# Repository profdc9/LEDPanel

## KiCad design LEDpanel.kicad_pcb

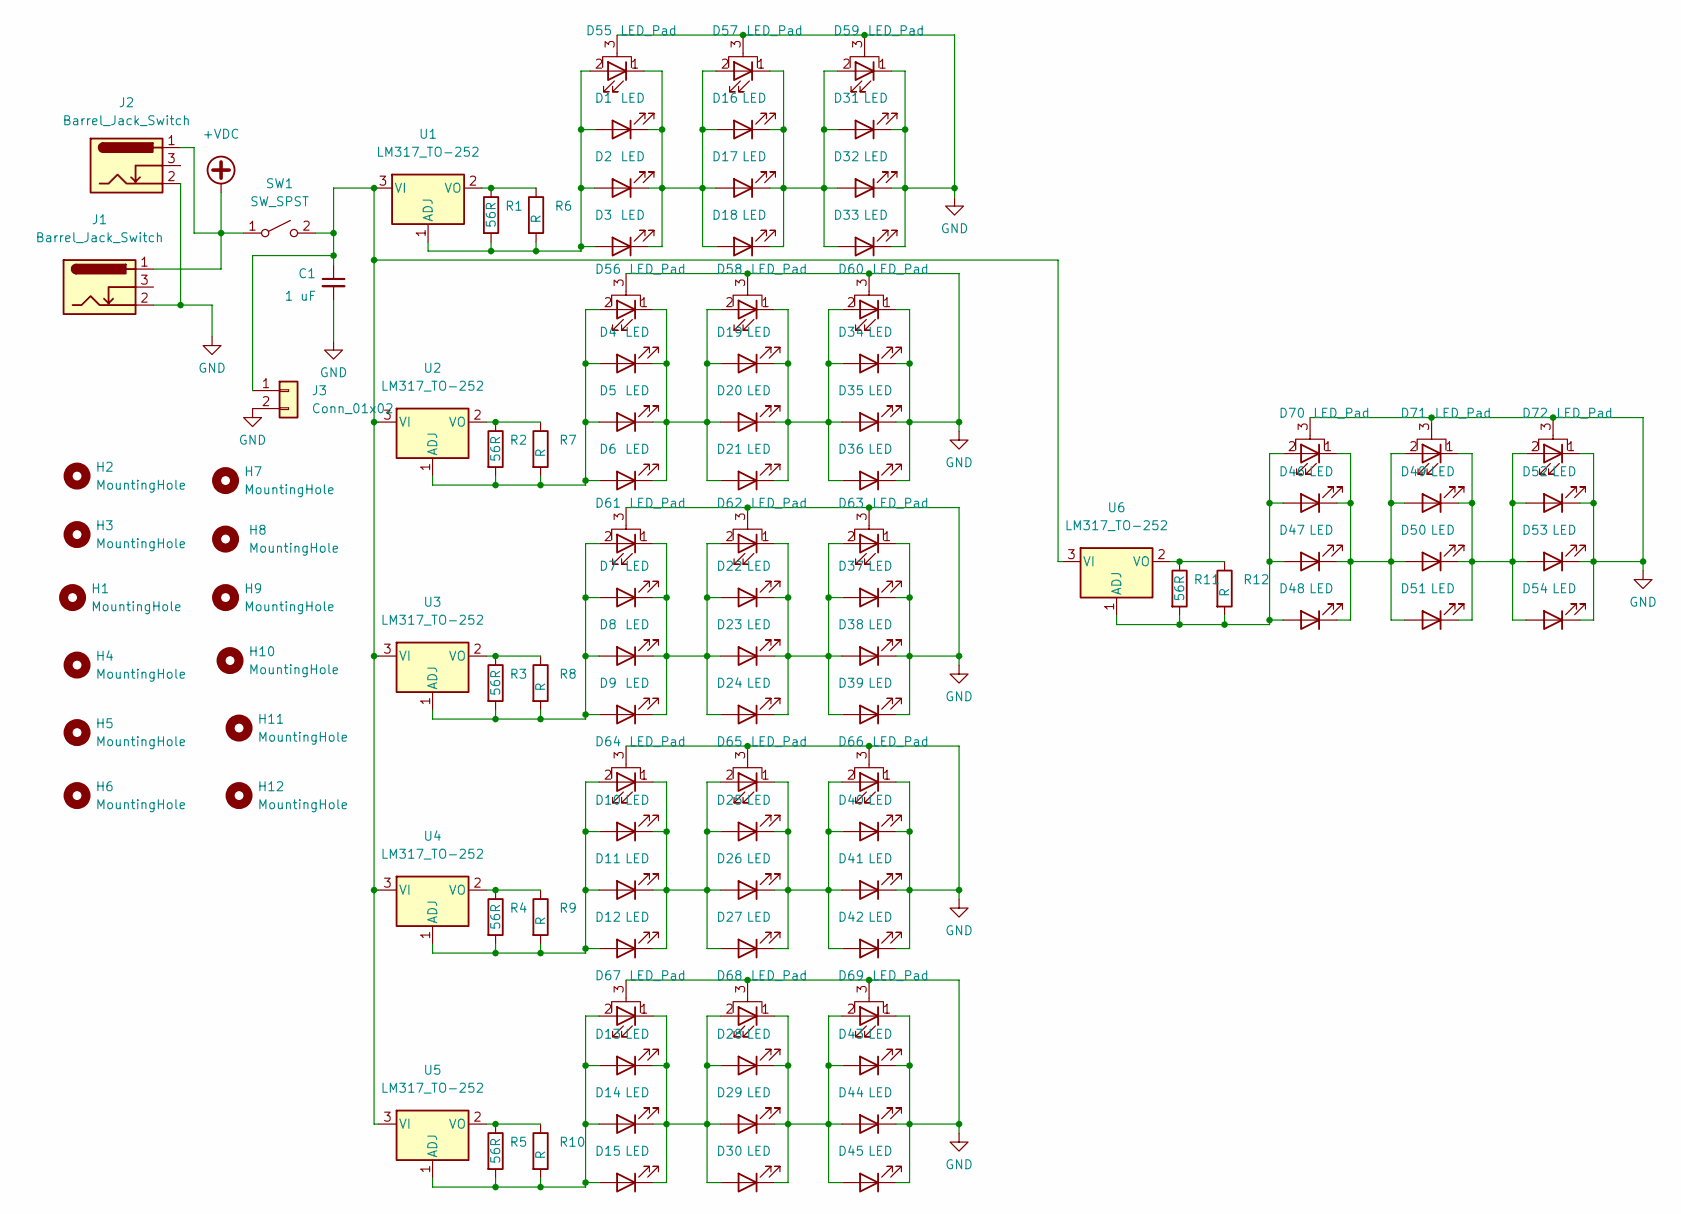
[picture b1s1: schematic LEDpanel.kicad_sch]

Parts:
C1: 1 uF; C_0805_2012Metric_Pad1.18x1.45mm_HandSolder; LCSC C28323
D1, D4, D7, D10, D13, D16, D19, D22, D25, D28, D31, D34, D37, D40, D43, D46, D49, D52: LED; LED_PLCC_2835_Handsoldering
D2, D5, D8, D11, D14, D17, D20, D23, D26, D29, D32, D35, D38, D41, D44, D47, D50, D53: LED; LED_0805_2012Metric_Pad1.15x1.40mm_HandSolder
D3, D6, D9, D12, D15, D18, D21, D24, D27, D30, D33, D36, D39, D42, D45, D48, D51, D54: LED; LED_D3.0mm
D55, D56, D57, D58, D59, D60, D61, D62, D63, D64, D65, D66, D67, D68, D69, D70, D71, D72: LED_Pad; LED_Cree-XP
H1, H4, H5, H6, H7, H9, H11, H12: MountingHole; MountingHole_4mm
H2, H3, H8, H10: MountingHole; MountingHole_3.2mm_M3
J1, J2: Barrel_Jack_Switch; BarrelJack_Horizontal
J3: Conn_01x02; TerminalBlock_Phoenix_MKDS-1,5-2-5.08_1x02_P5.08mm_Horizont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
R1, R2, R3, R4, R5, R11: 56R; R_0805_2012Metric_Pad1.20x1.40mm_HandSolder; LCSC C17757
R6, R7, R8, R9, R10, R12: R; R_Axial_DIN0207_L6.3mm_D2.5mm_P7.62mm_Horizontal
SW1: SW_SPST; TerminalBlock_Phoenix_MKDS-1,5-2-5.08_1x02_P5.08mm_Horizont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
U1, U2, U3, U4, U5, U6: LM317_TO-252; TO-252-2; LCSC C75510

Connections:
+VDC: J1.1, J2.1, SW1.1 (A)
GND: C1.2, D31.1 (K), D32.1 (K), D33.1 (K), D34.1 (K), D35.1 (K), D36.1 (K), D37.1 (K), D38.1 (K), D39.1 (K), D40.1 (K), D41.1 (K), D42.1 (K), D43.1 (K), D44.1 (K), D45.1 (K), D52.1 (K), D53.1 (K), D54.1 (K), D55.3 (PAD), D56.3 (PAD), D57.3 (PAD), D58.3 (PAD), D59.1 (K), D59.3 (PAD), D60.1 (K), D60.3 (PAD), D61.3 (PAD), D62.3 (PAD), D63.1 (K), D63.3 (PAD), D64.3 (PAD), D65.3 (PAD), D66.1 (K), D66.3 (PAD), D67.3 (PAD), D68.3 (PAD), D69.1 (K), D69.3 (PAD), D70.3 (PAD), D71.3 (PAD), D72.1 (K), D72.3 (PAD), J1.2, J2.2, J3.2
unnamed: C1.1, J3.1, SW1.2 (B), U1.3 (VI), U2.3 (VI), U3.3 (VI), U4.3 (VI), U5.3 (VI), U6.3 (VI)
unnamed: D1.1 (K), D2.1 (K), D3.1 (K), D16.2 (A), D17.2 (A), D18.2 (A), D55.1 (K), D57.2 (A)
unnamed: D4.2 (A), D5.2 (A), D6.2 (A), D56.2 (A), R2.2, R7.2, U2.1 (ADJ)
unnamed: D10.1 (K), D11.1 (K), D12.1 (K), D25.2 (A), D26.2 (A), D27.2 (A), D64.1 (K), D65.2 (A)
unnamed: D13.1 (K), D14.1 (K), D15.1 (K), D28.2 (A), D29.2 (A), D30.2 (A), D67.1 (K), D68.2 (A)
unnamed: D13.2 (A), D14.2 (A), D15.2 (A), D67.2 (A), R5.2, R10.2, U5.1 (ADJ)
unnamed: D16.1 (K), D17.1 (K), D18.1 (K), D31.2 (A), D32.2 (A), D33.2 (A), D57.1 (K), D59.2 (A)
unnamed: D19.1 (K), D20.1 (K), D21.1 (K), D34.2 (A), D35.2 (A), D36.2 (A), D58.1 (K), D60.2 (A)
unnamed: D4.1 (K), D5.1 (K), D6.1 (K), D19.2 (A), D20.2 (A), D21.2 (A), D56.1 (K), D58.2 (A)
unnamed: D22.1 (K), D23.1 (K), D24.1 (K), D37.2 (A), D38.2 (A), D39.2 (A), D62.1 (K), D63.2 (A)
unnamed: D7.1 (K), D8.1 (K), D9.1 (K), D22.2 (A), D23.2 (A), D24.2 (A), D61.1 (K), D62.2 (A)
unnamed: D25.1 (K), D26.1 (K), D27.1 (K), D40.2 (A), D41.2 (A), D42.2 (A), D65.1 (K), D66.2 (A)
unnamed: D28.1 (K), D29.1 (K), D30.1 (K), D43.2 (A), D44.2 (A), D45.2 (A), D68.1 (K), D69.2 (A)
unnamed: D46.1 (K), D47.1 (K), D48.1 (K), D49.2 (A), D50.2 (A), D51.2 (A), D70.1 (K), D71.2 (A)
unnamed: D46.2 (A), D47.2 (A), D48.2 (A), D70.2 (A), R11.2, R12.2, U6.1 (ADJ)
unnamed: D49.1 (K), D50.1 (K), D51.1 (K), D52.2 (A), D53.2 (A), D54.2 (A), D71.1 (K), D72.2 (A)
unnamed: R1.1, R6.1, U1.2 (VO)
unnamed: D1.2 (A), D2.2 (A), D3.2 (A), D55.2 (A), R1.2, R6.2, U1.1 (ADJ)
unnamed: R2.1, R7.1, U2.2 (VO)
unnamed: R3.1, R8.1, U3.2 (VO)
unnamed: D7.2 (A), D8.2 (A), D9.2 (A), D61.2 (A), R3.2, R8.2, U3.1 (ADJ)
unnamed: R4.1, R9.1, U4.2 (VO)
unnamed: D10.2 (A), D11.2 (A), D12.2 (A), D64.2 (A), R4.2, R9.2, U4.1 (ADJ)
unnamed: R5.1, R10.1, U5.2 (VO)
unnamed: R11.1, R12.1, U6.2 (VO)

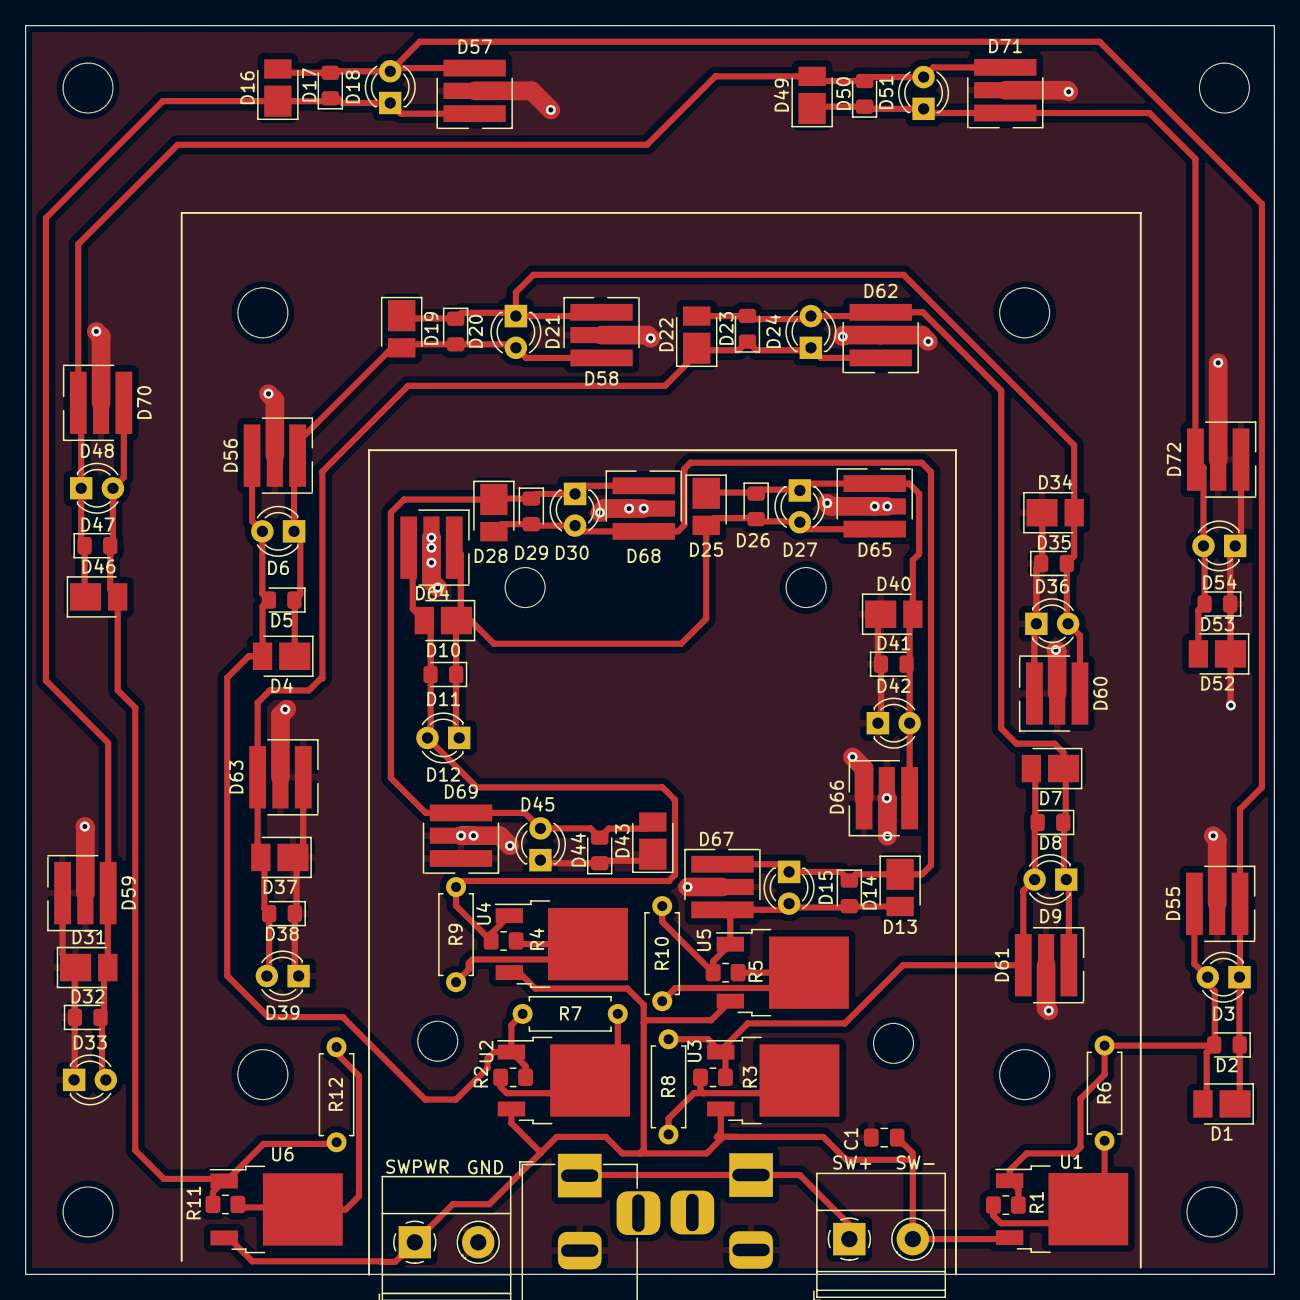
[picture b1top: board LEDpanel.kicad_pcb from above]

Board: 2 copper layers, 100.0 x 100.0 mm, 107 parts (1 on the bottom side), 27 nets.

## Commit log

2023-06-08 Distributed the components somewhat better
2023-06-08 Added silkscreen
